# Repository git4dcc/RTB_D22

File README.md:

# RTB_D22

My Homebrew [D22](https://rtb4dcc.de/hardware/decoder/d22/) decoder is a double sided mobile decoder with Plux16 connector. The decoder is designed to integrate into the [RTB](https://rtb4dcc.de/concept/) digital control infrastructure.

<details>
<summary>See also</summary>

- [RTB_D12 - custom](/../../../../RTB_D12) (Fleischmann V100)
- [RTB_D13 - custom](/../../../../git4dcc/RTB_D13) (Minitrix coach)
- [RTB_D15 - custom](/../../../../git4dcc/RTB_D15) (Minitrix V160)
- [RTB_D16 - NEM651](/../../../../git4dcc/RTB_D16)
- [RTB_D20 - NEM651](/../../../../git4dcc/RTB_D20)
- [RTB_D21 - Next18](/../../../../git4dcc/RTB_D21)
- [RTB_D23 - NEM652](/../../../../git4dcc/RTB_D23)

</details>

<details>
<summary>User Guides</summary>

- User Guide - DE
- [User Guide - EN](https://rtb4dcc.de/rtb_decoder_reference_en/)

</details>

<br>

## Decoder features,
- **Plux16** connector
- **DCC**
  - DCC-A automatic logon
  - DCC-R protocol extension
  - Service Mode Programming
- **Railcom**
  - Channel 1/2
  - POM, xPOM
  - DYN: Speed, QoS, Track-voltage, Motor-current, AUX-current, Temp, Distance travelled
- Double sided
- Dimension: 15 x 11 mm
- 7-20V track voltage
- heartbeat LED
- adjustable max motor current (default 300mA)
- adjustable max AUX current (default 500mA)
- over temp protection
- Function output: LF/LR (dimmable, 1.4kHz) open drain
- Function output: AUX1/AUX2 (dimmable, 1.4kHz) open drain
- Function output: AUX3/AUX4 logic level (3.3V) using LS A/B ports
- Function output: AUX5/AUX6 logic level (3.3V) or ZBCLK/ZBDAT (3.3V)
- optional external buffer capacitor
- <10mA idle power consumption
- Firmware update over main tracks via DCC-R protocol

# Hardware
The current PCB layout uses SMD footprints with 0.5mm pitch and 0402 parts. Reflow soldering is mandatory whereas handsoldering near to impossible.

## PCB
- 6-layer PCB, FR4, 15 x 11 x 0.8mm (double sided)
- CPU: AVR64DD28
- Motor bridge: DRV8231

## Kicad
[Schematic](doc/D22_schematic.pdf) | [Layout](doc/D22_layout.pdf) | [Gerber](production)

<details>
<summary>Dependency</summary>
<br>

:yellow_circle: Requires my Kicad project library [RTB_SamacSys](https://github.com/git4dcc/RTB_SamacSys) in the same directory tree.

</details>

## Firmware
Filename structure: { **pcb** }{ **code** }{ **version** }.hex

Example: **D22F0001**.hex

|   | Description |
| --- | --- |
| **pcb** | Name of matching hardware (**D22**) |
| **code** | Type of code contained (**R**=rom, **B**=bootloader, **F**=flash, **U**=bld update, **P**=UPDI factory code) |
| **version** | Release version (**####**) |

[Firmware files](firmware)

## UPDI
The fuse settings as well as the P-code (D22Pxxxx.hex) has to be installed by using UPDI.<br>
Connecting the decoder via its track pins to a 5V(DC) power supply will boot its CPU. This way, its easy to program the fuses and flash.

<details>
<summary>Details</summary>

| Fuse Setting | P-code Install |
| --- | --- |
|||

</details>

# Images
| top | bottom |
| --- | --- |
|  |  |

# YouTube
Some YouTubes to see the D22 decoder in action.<br><br>

This project is intended for hobby use only and is distributed in accordance with the Apache License 2.0 agreement.

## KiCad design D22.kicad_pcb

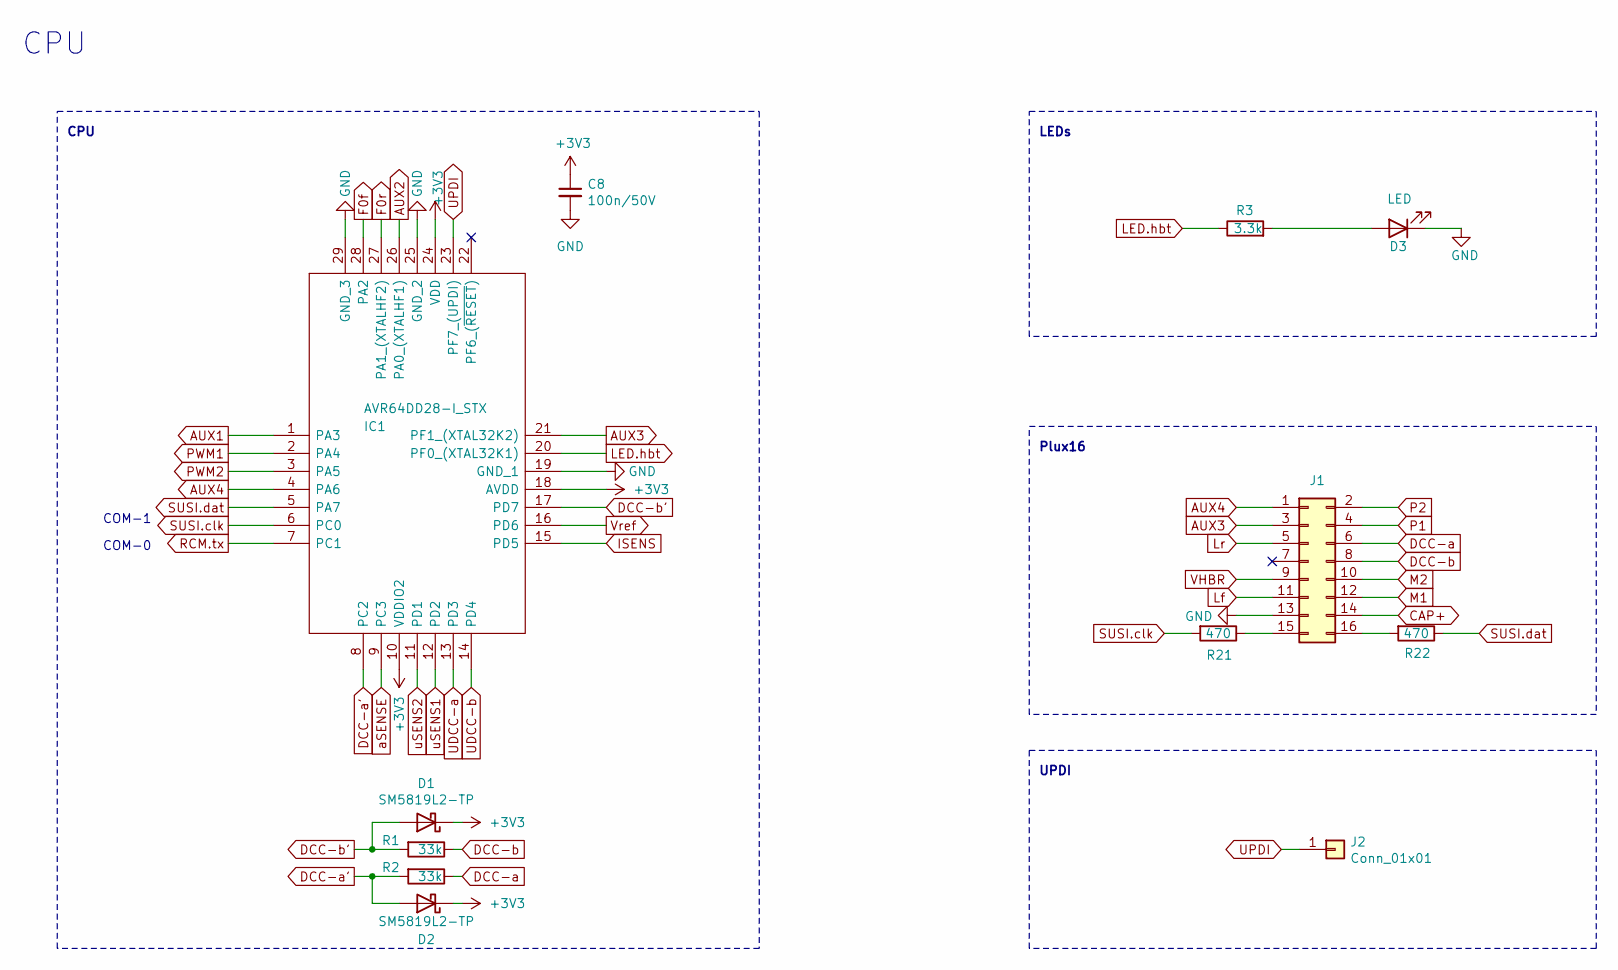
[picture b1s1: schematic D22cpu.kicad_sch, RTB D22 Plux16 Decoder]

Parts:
C8: 100n/50V; C_0402_1005Metric; LCSC Part # C307331
D1, D2: SM5819L2-TP; SM5819L2TP; LCSC Part # C6297199
D3: LED; LED_0402_1005Metric; LCSC Part # C130724
IC1: AVR64DD28-I_STX; QFN-28-1EP_4x4mm_P0.4mm_EP2.3x2.3mm; LCSC Part # C5156221
J1: Conn_02x08_Counter_Clockwise; PinHeader_2x08_P1.27mm_Vertical_SMD
J2: Conn_01x01; Solder 0.8 x 0.5
R1, R2: 33k; R_0402_1005Metric; LCSC Part # C25779
R3: 3.3k; R_0402_1005Metric; LCSC Part # C25900
R21, R22: 470; R_0402_1005Metric; LCSC Part # C25117

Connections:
+3V3: C8.1, D1.1 (K), D2.1 (K), IC1.10 (VDDIO2), IC1.18 (AVDD), IC1.24 (VDD); also elsewhere on the board
AUX1: IC1.1 (PA3); also elsewhere on the board
AUX2: IC1.26 (PA0_(XTALHF1)); also elsewhere on the board
AUX3: IC1.21 (PF1_(XTAL32K2)), J1.3
AUX4: IC1.4 (PA6), J1.1
CAP+: J1.14; also elsewhere on the board
CAP_ENA: IC1.5 (PA7), R22.1; also elsewhere on the board
DCC-a: J1.6, R2.1; also elsewhere on the board
DCC-a': D2.2 (A), IC1.8 (PC2), R2.2
DCC-b: J1.8, R1.1; also elsewhere on the board
DCC-b': D1.2 (A), IC1.17 (PD7), R1.2
F0f: IC1.28 (PA2); also elsewhere on the board
F0r: IC1.27 (PA1_(XTALHF2)); also elsewhere on the board
GND: C8.2, D3.1 (K), IC1.19 (GND_1), IC1.25 (GND_2), IC1.29 (GND_3), J1.13; also elsewhere on the board
ISENS: IC1.15 (PD5); also elsewhere on the board
LED.hbt: IC1.20 (PF0_(XTAL32K1)), R3.1
Lf: J1.11; also elsewhere on the board
Lr: J1.5; also elsewhere on the board
M1: J1.12; also elsewhere on the board
M2: J1.10; also elsewhere on the board
unnamed: D3.2 (A), R3.2
unnamed: J1.15, R21.1
unnamed: J1.16, R22.2
P1: J1.4; also elsewhere on the board
P2: J1.2; also elsewhere on the board
PWM1: IC1.2 (PA4); also elsewhere on the board
PWM2: IC1.3 (PA5); also elsewhere on the board
RCM.tx: IC1.7 (PC1); also elsewhere on the board
SUSI.clk: IC1.6 (PC0), R21.2
UDCC-a: IC1.13 (PD3); also elsewhere on the board
UDCC-b: IC1.14 (PD4); also elsewhere on the board
UPDI: IC1.23 (PF7_(UPDI)), J2.1 (Pin_1_1)
VHBR: J1.9; also elsewhere on the board
Vref: IC1.16 (PD6); also elsewhere on the board
aSENSE: IC1.9 (PC3); also elsewhere on the board
uSENS1: IC1.12 (PD2); also elsewhere on the board
uSENS2: IC1.11 (PD1); also elsewhere on the board

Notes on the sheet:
Plux16
COM-0
COM-1
CPU
LEDs
UPDI

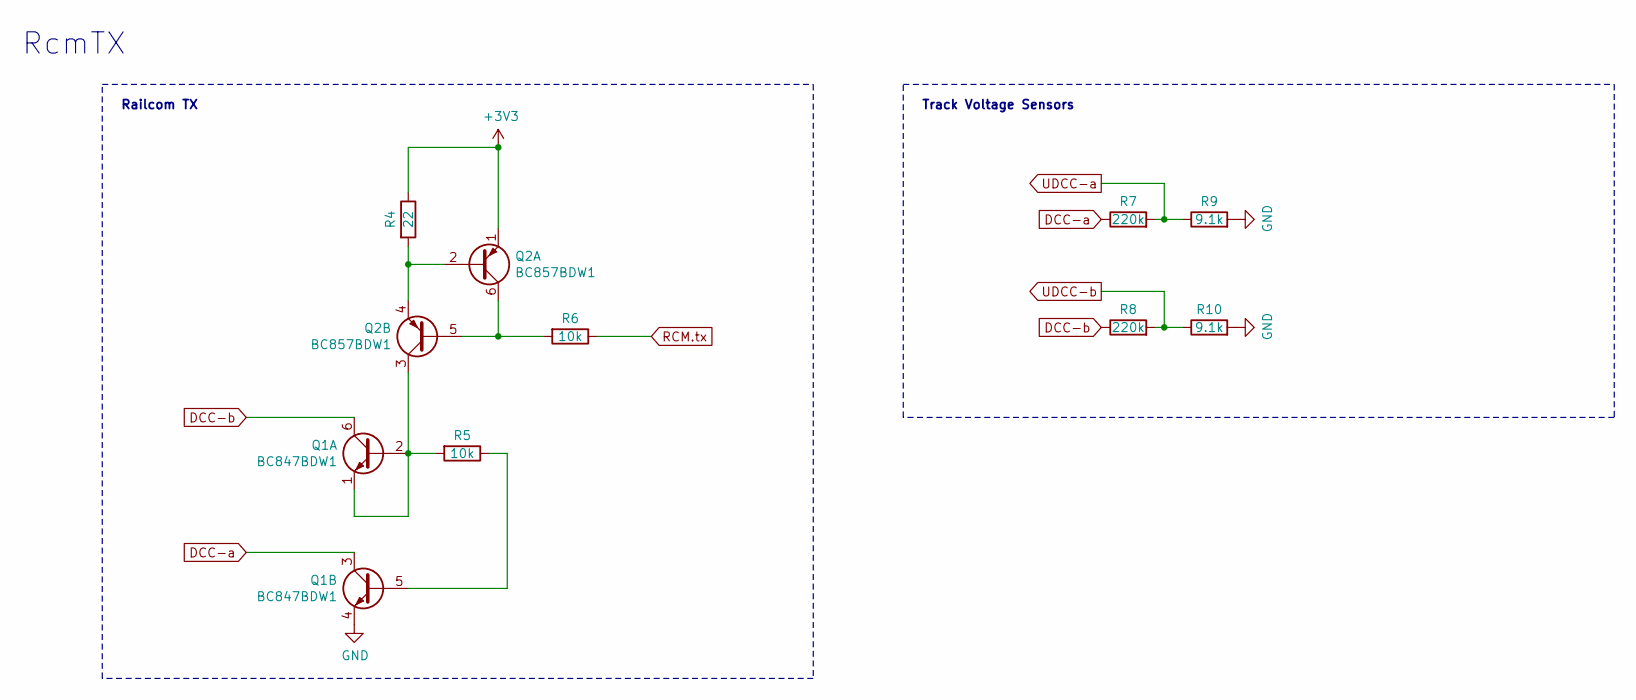
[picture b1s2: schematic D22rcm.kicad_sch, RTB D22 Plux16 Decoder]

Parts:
Q1: BC847BDW1; SOT-666; LCSC Part # C455062
Q2: BC857BDW1; SOT-666; LCSC Part # C282521
R4: 22; R_0402_1005Metric; LCSC Part # C25092
R5, R6: 10k; R_0402_1005Metric; LCSC Part # C25744
R7, R8: 220k; R_0402_1005Metric; LCSC Part # C25767
R9, R10: 9.1k; R_0402_1005Metric; LCSC Part # C163450

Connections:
+3V3: Q2.1 (E1), R4.1; also elsewhere on the board
DCC-a: Q1.3 (C2), R7.1; also elsewhere on the board
DCC-b: Q1.6 (C1), R8.1; also elsewhere on the board
GND: Q1.4 (E2), R9.2, R10.2; also elsewhere on the board
unnamed: Q1.1 (E1), Q1.2 (B1), Q2.3 (C2), R5.2
unnamed: Q1.5 (B2), R5.1
unnamed: Q2.2 (B1), Q2.4 (E2), R4.2
unnamed: Q2.5 (B2), Q2.6 (C1), R6.2
RCM.tx: R6.1; also elsewhere on the board
UDCC-a: R7.2, R9.1; also elsewhere on the board
UDCC-b: R8.2, R10.1; also elsewhere on the board

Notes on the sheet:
Railcom TX
Track Voltage Sensors
RcmTX

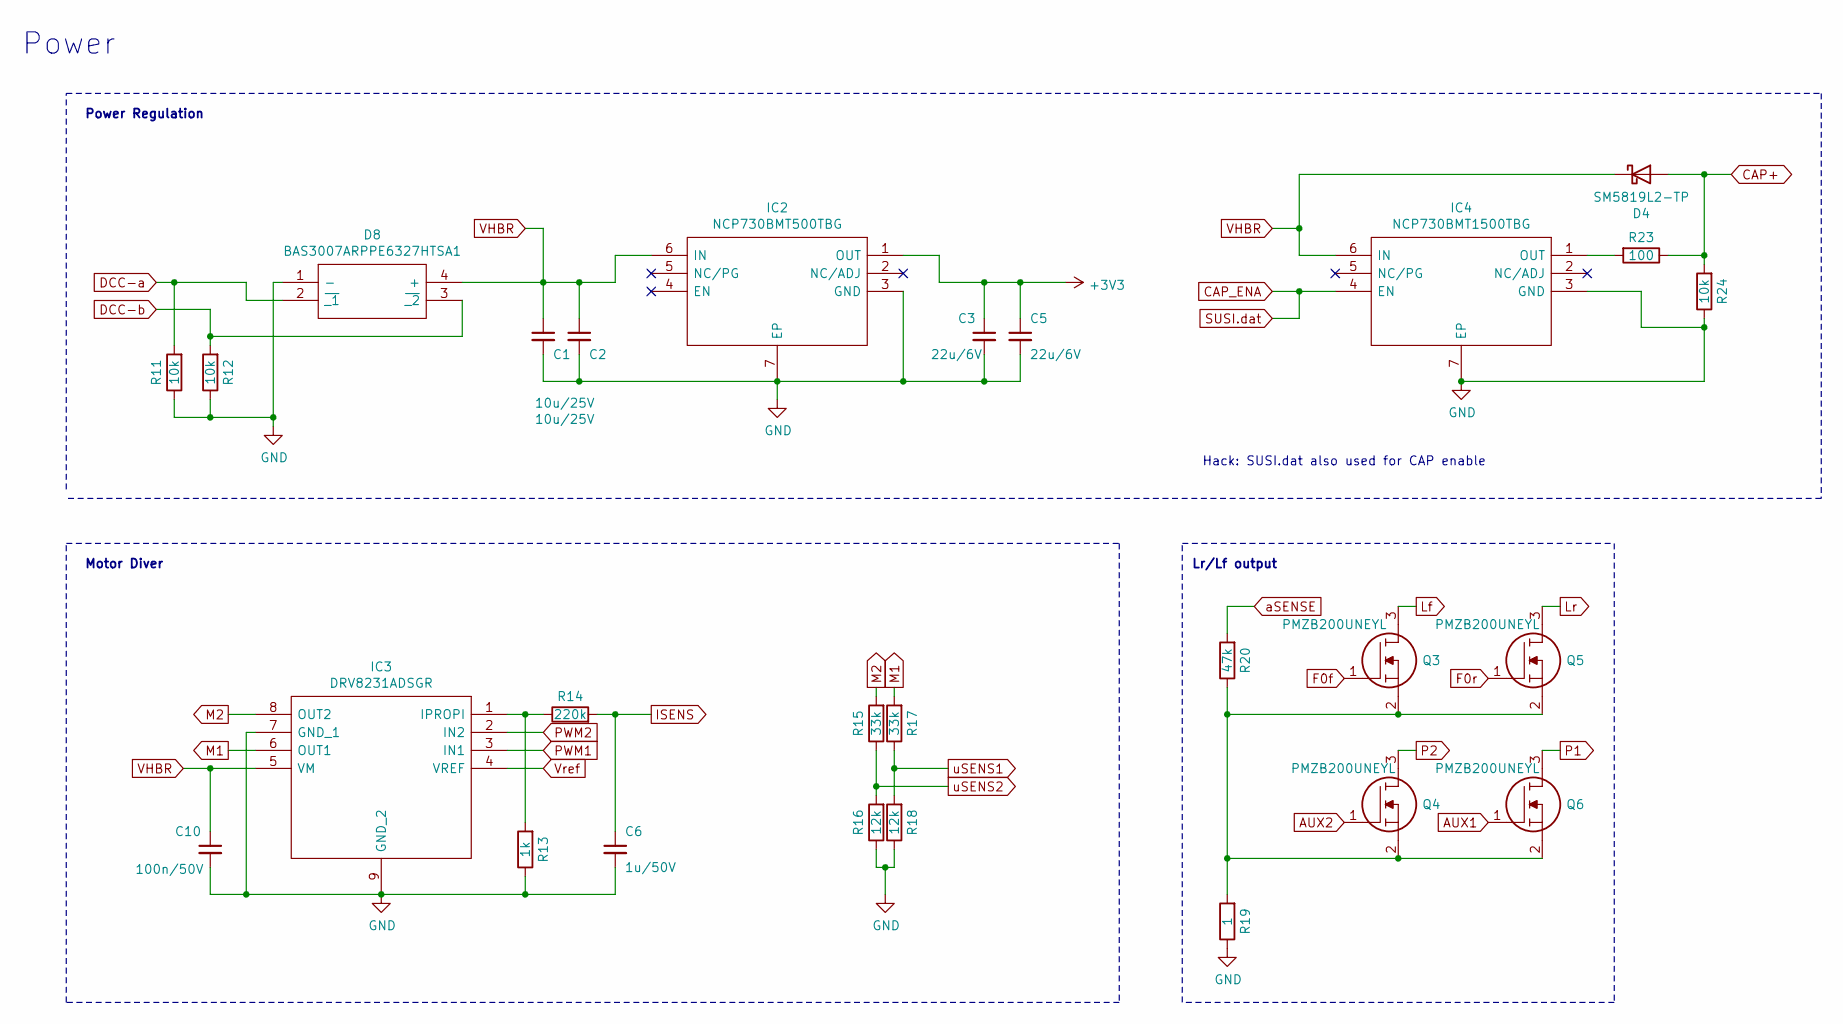
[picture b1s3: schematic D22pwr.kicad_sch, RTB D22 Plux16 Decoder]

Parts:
C1, C2: 10u/25V; C_0603_1608Metric; LCSC Part # C96446
C3, C5: 22u/6V; C_0603_1608Metric; LCSC Part # C59461
C6: 1u/50V; C_0402_1005Metric; LCSC Part # C52923
C10: 100n/50V; C_0402_1005Metric; LCSC Part # C307331
D4: SM5819L2-TP; SM5819L2TP; LCSC Part # C6297199
D8: BAS3007ARPPE6327HTSA1; BF998215; LCSC Part # C6430958
IC2: NCP730BMT500TBG; WSON-6-1EP_2x2mm_P0.65mm_EP1x1.6mm; LCSC Part # C892822
IC3: DRV8231ADSGR; SON50P200X200X80-9N; LCSC Part # C5139865
IC4: NCP730BMT1500TBG; WSON-6-1EP_2x2mm_P0.65mm_EP1x1.6mm; LCSC Part # C892817
Q3, Q4, Q5, Q6: PMZB200UNEYL; Diodes_DFN1006-3; LCSC Part # C547292
R11, R12, R24: 10k; R_0402_1005Metric; LCSC Part # C25744
R13: 1k; R_0402_1005Metric; LCSC Part # C11702
R14: 220k; R_0402_1005Metric; LCSC Part # C25767
R15, R17: 33k; R_0402_1005Metric; LCSC Part # C25779
R16, R18: 12k; R_0402_1005Metric; LCSC Part # C25752
R19: 1; R_0603_1608Metric; LCSC Part # C22936
R20: 47k; R_0402_1005Metric; LCSC Part # C25792
R23: 100; R_0603_1608Metric; LCSC Part # C22775

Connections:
+3V3: C3.1, C5.1, IC2.1 (OUT); also elsewhere on the board
AUX1: Q6.1; also elsewhere on the board
AUX2: Q4.1; also elsewhere on the board
CAP+: D4.2 (A), R23.1, R24.2; also elsewhere on the board
CAP_ENA: IC4.4 (EN); also elsewhere on the board
DCC-a: D8.2 (~_1), R11.2; also elsewhere on the board
DCC-b: D8.3 (~_2), R12.2; also elsewhere on the board
F0f: Q3.1; also elsewhere on the board
F0r: Q5.1; also elsewhere on the board
GND: C1.2, C2.2, C3.2, C5.2, C6.2, C10.2, D8.1 (-), IC2.3 (GND), IC2.7 (EP), IC3.7 (GND_1), IC3.9 (GND_2), IC4.3 (GND), IC4.7 (EP), R11.1, R12.1, R13.1, R16.1, R18.1, R19.1, R24.1; also elsewhere on the board
ISENS: C6.1, R14.2; also elsewhere on the board
Lf: Q3.3; also elsewhere on the board
Lr: Q5.3; also elsewhere on the board
M1: IC3.6 (OUT1), R17.2; also elsewhere on the board
M2: IC3.8 (OUT2), R15.2; also elsewhere on the board
unnamed: IC3.1 (IPROPI), R13.2, R14.1
unnamed: IC4.1 (OUT), R23.2
unnamed: Q3.2, Q4.2, Q5.2, Q6.2, R19.2, R20.1
P1: Q6.3; also elsewhere on the board
P2: Q4.3; also elsewhere on the board
PWM1: IC3.3 (IN1); also elsewhere on the board
PWM2: IC3.2 (IN2); also elsewhere on the board
VHBR: C1.1, C2.1, C10.1, D4.1 (K), D8.4 (+), IC2.6 (IN), IC3.5 (VM), IC4.6 (IN); also elsewhere on the board
Vref: IC3.4 (VREF); also elsewhere on the board
aSENSE: R20.2; also elsewhere on the board
uSENS1: R17.1, R18.2; also elsewhere on the board
uSENS2: R15.1, R16.2; also elsewhere on the board

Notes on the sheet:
Power
Power Regulation
Motor Diver
Lr/Lf output
Hack: SUSI.dat also used for CAP enable

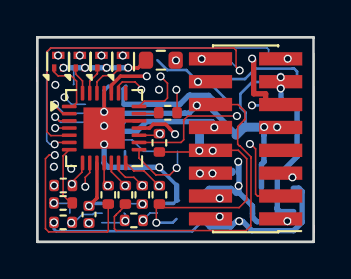
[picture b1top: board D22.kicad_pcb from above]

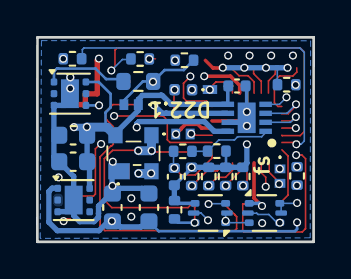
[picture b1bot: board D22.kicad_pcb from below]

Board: 6 copper layers, 15.3 x 11.4 mm, 48 parts (30 on the bottom side), 44 nets.

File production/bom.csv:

Designator,Footprint,Quantity,Value,LCSC Part #
"C1, C2",0603,2,10u/25V,C96446
"C10, C8",0402,2,100n/50V,C307331
"C3, C5",0603,2,22u/6V,C59461
C6,0402,1,1u/50V,C52923
"D1, D2, D4",SM5819L2TP,3,SM5819L2-TP,C6297199
D3,0402,1,LED,C130724
D8,BF998215,1,BAS3007ARPPE6327HTSA1,C6430958
IC1,QFN-28-1EP_4x4mm_P0.4mm_EP2.3x2.3mm,1,AVR64DD28-I_STX,C5156221
IC2,WSON-6-1EP_2x2mm_P0.65mm_EP1x1.6mm,1,NCP730BMT500TBG,C892822
IC3,SON50P200X200X80-9N,1,DRV8231ADSGR,C5139865
IC4,WSON-6-1EP_2x2mm_P0.65mm_EP1x1.6mm,1,NCP730BMT1500TBG,C892817
J1,PinHeader_2x08_P1.27mm_Vertical_SMD,1,Conn_02x08_Counter_Clockwise,
J2,Solder 0.8 x 0.5,1,Conn_01x01,
Q1,SOT-666,1,BC847BDW1,C455062
Q2,SOT-666,1,BC857BDW1,C282521
"Q3, Q4, Q5, Q6",Diodes_DFN1006-3,4,PMZB200UNEYL,C547292
"R1, R15, R17, R2",0402,4,33k,C25779
"R10, R9",0402,2,9.1k, C163450
"R11, R12, R24, R5, R6",0402,5,10k,C25744
R13,0402,1,1k,C11702
"R14, R7, R8",0402,3,220k,C25767
"R16, R18",0402,2,12k,C25752
R19,0603,1,1,C22936
R20,0402,1,47k,C25792
"R21, R22",0402,2,470,C25117
R23,0603,1,100,C22775
R3,0402,1,3.3k,C25900
R4,0402,1,22,C25092

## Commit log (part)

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2024-11-28 initial
2025-03-22 add: decoder lock
2025-07-31 add: fuses
2025-07-31 add: updi description
2025-08-05 mod: led automation
2025-10-02 fix: SUSI/AUX
2026-02-20 Update links in README.md to relative paths
2026-02-20 git mirror test
2026-06-26 updated Kicad version

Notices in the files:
D22.kicad_pcb:
Licensed under the Apache License, Version 2
